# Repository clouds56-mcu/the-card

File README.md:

# The Card — E-Paper Smart Badge

**Website:** <https://clouds56-mcu.github.io/the-card/>

> An **ESP32-S3** based DIY/learning smart badge: e-paper wallpapers, Bluetooth, NFC, multi-button watch-style control, and on-board sensors, worn around the neck like an ID badge.

## 📋 Project Brief

| Item | Spec |
|---|---|
| **Positioning** | DIY / open learning platform (open-source, flashable, well-documented) |
| **MCU** | ESP32-S3-WROOM-1-N16R8 (16 MB Flash + 8 MB Octal PSRAM) |
| **Display** | 2.9" e-paper 296×128 (SSD1680, partial refresh / 4-gray) |
| **Wireless** | Bluetooth 5 LE (on-module) + NFC (ST25DV04KC dynamic tag, etched v0.2 antenna) |
| **Input** | 4× tactile buttons (up/down/select/menu, watch-style) |
| **Sensors** | 6-axis IMU (LSM6DSO) + Temp/Humidity (SHT40) |
| **Power** | 3.7 V Li-Po + USB-C charging + fuel gauge |
| **Wear** | Lanyard badge form factor |

## 📚 Documentation Index

| Doc | Description |
|---|---|
| [docs/architecture.md](docs/architecture.md) | System block diagram, subsystem design, **GPIO pin map** |
| [docs/bom.md](docs/bom.md) | Full BOM (with LCSC part #s / unit prices / links) + cost analysis |
| [docs/power-budget.md](docs/power-budget.md) | State-based power model + battery-life scenarios |
| [website/README.md](website/README.md) | Product site, hardware previews, and candidate release downloads |

## 💰 Key Takeaways

- **Component BOM (incl. panel + battery, excl. PCB/case):** ~$29 (1-off) / ~$21 (@100) / ~$18 (@1k)
- **Landed cost (incl. PCBA + case + assembly):** ~$40 (1-off) / ~$28 (@100) / ~$21 (@1k)
- **Cost driver:** e-paper panel (~$7, 33%) + MCU (~$4, 18%) + battery/IMU (~$2.5 each)
- **Battery life:** ~5.4 months theoretical for modeled daily use (1000 mAh), with ~4–5 months as a planning range; prototype measurement is pending
- **#1 power gotcha:** keep the WS2812 gated; the always-enabled SO-8 ST25DV and ME6211 dominate the revised ~0.16–0.17 mA sleep estimate

## 🚧 Optional Expansion (not in core BOM)

- Microphone (INMP441 / MSM261S) — voice interaction
- Ambient light (BH1750) — auto contrast
- Solar harvesting (paired with ST25DV's EH pin)
- Color e-paper (2.66" R/Y/B/W, slow 11 s refresh)

---

## 📄 License

This project is released under the **[MIT License](LICENSE)** — firmware, hardware designs, and documentation alike. Build it, modify it, ship it.

---

*Prices reflect 2026-08 LCSC / JLCPCB / Good Display market data and are for reference only — confirm at order time.*

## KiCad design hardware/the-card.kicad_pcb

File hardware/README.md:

# hardware/ — Schematic & PCB (KiCad, code-first)

The electrical design of **the-card**, captured in code and emitted as both a
KiCad **schematic** (`.kicad_sch`) and a **netlist** (`.net`). KiCad 10 is
installed; the schematic opens in eeschema and is ERC-clean (0 errors).

```
hardware/
├── parts.yaml              # parts/procurement manifest, kept in sync with circuit.py
├── design_metadata.py      # sole project/design SemVer identity
├── pyproject.toml + uv.lock# uv project: skidl + easyeda2kicad (+ pypdf dev)
├── circuit.py              # the design in SKiDL (connectivity) -> the-card.net
├── gen_hierarchical_schematic.py # current deterministic A2 layout generator
├── gen_pcb.py              # deterministic placement, routing, planes, and keepouts
├── pcb_router.py           # board-specific fanout and deterministic maze routing
├── nfc_antenna.py          # v0.2 coil geometry and first-order RF model
├── verify_schematic.py     # compare every KiCad pin's peers with circuit.py
├── gen_schematic.py        # legacy flat-layout generator; not used currently
├── the-card.kicad_pro      # KiCad 10 project
├── the-card.kicad_sch      # GENERATED single-page A2 schematic
├── the-card.kicad_pcb      # GENERATED four-layer PCB layout
├── the-card.kicad_dru      # project DRC rules, including the NFC quiet area
├── sym-lib-table / fp-lib-table  # register our the-card + passives libraries
├── SCHEMATIC-GUIDE.md      # functional-region drawing and review notes
├── datasheets/             # archived datasheet PDFs + index
├── scripts/fetch_libs.sh   # regenerate libraries/ from LCSC#s in parts.yaml
├── scripts/normalize_libraries.py # reviewed corrections to fetched footprints
├── scripts/release_fabrication.py # checked Gerber/drill/BOM/placement release
├── scripts/export_design_review.py # portable CI schematic/PCB review exports
├── scripts/release_manifest.py # versioned release.json metadata + hashes
├── scripts/rasterize_svg.py # review PNGs from KiCad SVG plots
└── libraries/              # Reviewed 2D libs tracked; generated 3D models ignored
```

## One-time setup

```bash
cd hardware
uv sync                     # create .venv, install skidl + easyeda2kicad
./scripts/fetch_libs.sh     # fetch symbol/footprint/3D for every LCSC part
```

## Generate and verify

```bash
uv run python circuit.py
uv run python gen_hierarchical_schematic.py
uv run python verify_schematic.py
kicad-cli sch erc --severity-all --output /tmp/erc.json --format json the-card.kicad_sch
```

The verifier exports the complete KiCad schematic and compares both the peer
set of every component pin and every explicitly named net with the canonicalized
SKiDL circuit. The expected v0.2.0 result is 78 components and 292 component
pins with identical connectivity across 43 canonical named nets. KiCad ERC has 0
violations.

Generate the PCB layout with KiCad's bundled Python:

```bash
/Applications/KiCad/KiCad.app/Contents/Frameworks/\
Python.framework/Versions/3.9/bin/python3 gen_pcb.py
kicad-cli pcb drc --output /tmp/pcb-drc.json --format json the-card.kicad_pcb
```

The board is a portrait ID-1 outline (53.98 × 85.60 mm), four layers, and
0.8 mm thick. The display and controls are on the front; the ESP32, battery,
sensors, power circuitry, USB-C, and display connector are on the rear. The
generator encodes display, 603048 battery, ESP32 antenna, and NFC keepouts. The
NFC coil occupies a dedicated all-copper-layer RF quiet area: only `NFC_AC0`
and `NFC_AC1` antenna copper is allowed there, with no ground or power plane
beneath it. F.Cu and B.Cu carry local signals over ground pours, In1.Cu is the
primary ground plane, and In2.Cu is the primary 3V3 plane plus longer signal
routes. Ground stitching ties the pours together. The generated board is fully
routed and passes KiCad DRC with 0 violations and 0 unconnected items. Four
non-fabrication reference images are embedded beside the board in PCB Editor,
showing F.Cu, In1.Cu, In2.Cu, and B.Cu simultaneously without affecting plots.

## CI design review

For every CI run, `.github/workflows/ci.yml` publishes a short-lived
`design-review-<commit>` artifact after ERC and DRC pass. It contains the
schematic as PDF/SVG/PNG, a thumbnail, a multipage PCB PDF, and front, inner,
and mirrored back PCB PNGs. These files make schematic and layout changes easy
to inspect without KiCad; they are previews from one commit, not approved
fabrication outputs. The separate `kicad-reports` artifact retains the ERC and
DRC JSON reports, including reports from failed runs when available.

Run the manual `Hardware output` workflow when a complete candidate handoff is
needed. It rebuilds all release gates in the pinned KiCad environment and
uploads the fabrication, preview, assembly, reports, manifest, and checksums as
one 30-day Actions artifact. The workflow does not publish a GitHub Release or
mark the physical approval gates complete.

Build a manufacturing handoff into a new directory after generation:

```bash
uv run python scripts/release_fabrication.py \
  --output ../outputs/the-card-hardware-v0.2.0
```

`DESIGN_VERSION` in `design_metadata.py` is the sole maintained identity. It is
written in full to both KiCad title blocks and release metadata; the constrained
PCB silkscreen derives the matching major/minor mark (`HW 0.2`). Before 1.0, a
physical/electrical/mechanical PCB change advances the minor version, while an
artifact-only correction may advance the patch version. Never overwrite an
already published version. The first physically validated design can become
v1.0.0. The earlier v0.1.0 draft is retained only in Git history because it was
never ordered and contains the NFC issue corrected in v0.2.0.

The release command refuses to overwrite an existing directory or use a dirty
worktree. It runs the connectivity and canonical-net-name verifier, then
requires a clean full DRC, schematic parity check, and ERC. The output tree is:

```text
fabrication/       # Gerbers, PTH/NPTH drills, notes, fabrication-only ZIP
preview/           # schematic/PCB PDFs and PNGs, layer/drill plots, preview ZIP
assembly/
├── canonical/     # normalized BOM/placement CSV+JSON and assembly drawings
└── jlcpcb/        # upload-ready BOM and position CSVs
reports/           # ERC, DRC/parity, and drill reports
release.json       # release identity, provenance, validation, pending approval
SHA256SUMS         # hashes for every artifact and release.json
```

Pass `--include-3d` only when all ignored supplier 3D models referenced by the
board are present and reviewed. Without it, the release remains complete for
fabrication and assembly and uses 2D previews generated from tracked design
files. The internal assembly BOM reports unresolved sourcing explicitly; a
clean board does not imply that every row is ready for a turnkey PCBA order. See
[`FABRICATION.md`](FABRICATION.md) before sending any files to a board house.

`assembly/jlcpcb/bom.csv` follows JLC's eight-column
`Comment, Description, Designator, Footprint, LibRef, Pins, Quantity, JLCPCB Part #`
format. Exact LCSC/JLC codes are written to `JLCPCB Part #` when assigned.
`assembly/jlcpcb/positions.csv` is the matching millimetre CPL with
`Designator, Mid X, Mid Y, Rotation, Layer` and normalized `Top`/`Bottom`
layer names.

Open the schematic:
```bash
/Applications/KiCad/KiCad.app/Contents/MacOS/eeschema the-card.kicad_sch
```

> `gen_hierarchical_schematic.py` is retained under its original filename, but it
> now emits one A2 sheet. It overwrites `the-card.kicad_sch`; put durable layout
> changes into its placement and region-offset tables so regeneration stays
> deterministic. `gen_schematic.py` is the previous flat A1 generator and is
> retained only as a reference.

## How it fits together

`parts.yaml` holds procurement and part data. Its `lcsc_parts` section drives
EasyEDA library fetching, while `assembly_parts` records exact BOM selections
that reuse existing project or KiCad symbols and footprints. An
`assembly_parts` entry with the same reference as an `lcsc_parts` entry
overrides only the procurement selection, allowing a verified pin-compatible
replacement to keep the existing symbol and footprint. `fetch_libs.sh`
builds the two KiCad libraries, while `circuit.py` defines electrical
connectivity and emits `the-card.net`. The layout generator imports that circuit
and changes only its presentation: one A2 page containing Power/USB, MCU,
NFC/sensors, e-paper, and UI
regions. For an electrical change, update `circuit.py`, regenerate the netlist and
schematic, then run `verify_schematic.py` before accepting the result. See
[`FABRICATION.md`](FABRICATION.md) for stackup, ordering, and assembly checks.

Every resistor and capacitor also receives hidden `Related To` and `Function`
properties from `circuit.py`. The single-page schematic shows compact functional
callouts, while KiCad properties and the internal assembly BOM retain the exact
per-reference annotations without crowding the drawing. The layout keeps support
passives beside their related blocks and emits explicit dots at true wire
junctions; visually crossing wires without a dot are not connected.

## Verification status (done)

The originally flagged sections were checked against datasheets (see
`../PROGRESS.md` §7 and the full pinout cross-check). The bare panel's required
SSD1680 booster, 25 V pump capacitors, and 50 V rail bypass network are now
present on the host PCB. Residual
PCB-layout items are:

- **ST25DV04KC antenna** — design v0.2.0 uses a nine-turn, 0.20 mm F.Cu spiral in the
  front-left strip, with a dedicated quiet area on all four copper layers. The
  ST square-equivalent heuristic gives about 4.52 µH; an NXP rectangular-coil
  cross-check brackets about 3.19–3.98 µH and implies roughly 6.1–14.7 pF of
  nominal added capacitance before stray/assembly loading. C29 therefore accepts
  0–22 pF C0G/NP0, but remains unpopulated until measurement. Verify resonance,
  Q, and multi-phone read/write range in the final enclosure; treat more than
  about 15–18 pF, poor Q, or inadequate range as an antenna-respin signal.
- **Display FPC** — J2 is now the verified single-row Hirose
  FH12-24S-0.5SH(55): 24 positions, 0.5 mm pitch, bottom contact, for a 0.30 mm
  FPC. The project footprint numbers its two hold-down tabs 25 and 26 so both
  are tied to ground by the schematic. Rear silkscreen marks pin 1; confirm the
  folded panel orientation with a paper or physical mock-up before ordering.
- **JST-PH battery polarity** — rear silkscreen marks `BAT+` and `BAT-`, but the
  selected pack's cable must still be verified before plugging it in.

The DW01A/HXY 8205A protection stage has been checked against both datasheets:
R9=100 Ω, R10=1 kΩ, DOUT drives G1 on the cell-negative side, and COUT drives
G2 on the pack-negative side.

## Gotchas

- **easyeda2kicad 1.0.1:** `--output` must be **absolute** with
  `--project-relative` (relative paths crash). `fetch_libs.sh` handles this.
- **EasyEDA API 403:** rate-limits after a big batch — re-run in a few minutes.
- **SKiDL reports pin Y inverted** vs KiCad (math y-up vs KiCad y-down); the
  layout generator handles KiCad's screen-coordinate rotations explicitly.
- **ESP32-S3-WROOM-1-N16R8** uses GPIO33–37 for its Octal PSRAM;
  `circuit.py` leaves GPIO35–37 unconnected and uses GPIO16 for `EPD_PWR_EN`.
- The ST25DV SO-8 GPO is open-drain. Design v0.2.0 adds its required 10 kΩ pull-up R17
  and routes `NFC_IRQ` to GPIO21; GPIO3 is deliberately unused because it is a
  strap-sensitive pin.
- The generator sets embedded part pins to `passive` because several EasyEDA
  symbols have incorrect electrical types. `verify_schematic.py` independently
  checks actual connectivity rather than relying on those types.

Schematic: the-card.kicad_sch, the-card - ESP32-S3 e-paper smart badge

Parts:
C1, C4, C7, C10, C11, C12, C14, C15, C16, C17, C18, C19: 100nF; C_0402_1005Metric
C2, C5, C6, C13: 10uF; C_0603_1608Metric
C3, C8, C9: 1uF; C_0603_1608Metric
C20, C21: 4.7uF 25V; C_0805_2012Metric
C22, C23, C24, C25, C26, C27, C28: 1uF 50V; C_0805_2012Metric
C29: DNP 0-22pF C0G/NP0; C_0402_1005Metric; not fitted
D1: WS2812B-MINI; LED-SMD_4P-L3.5-W3.5-TL_WS2812B
D2, D3, D4: LMBR0530T1G; D_SOD-123
J1: TYPE-C-31-M-12; USB-C_SMD-TYPE-C-31-M-12_1
J2: FH12-24S-0.5SH(55); Hirose_FH12-24S-0.5SH_1x24-2MP_P0.50mm_Horizontal
J3: S2B-PH-SM4-TB(LF)(SN); JST_PH_S2B-PH-SM4-TB_1x02-1MP_P2.00mm_Horizontal
L1: XRNR5020-47uH/M 47uH; IND-SMD_L5.0-W5.0_XRNR5020
L2: PCB NFC antenna; NetTie-2_SMD_Pad0.5mm
Q1, Q2: SI2301CDS-T1-GE3; SOT-23-3_L3.0-W1.7-P0.95-LS2.9-BR
Q3: SI1308EDL-T1-GE3; SOT-323_SC-70
R1, R2, R8, R11, R12, R17: 10k; R_0402_1005Metric
R3, R15: 1M; R_0402_1005Metric
R4: 300k; R_0402_1005Metric
R5, R6: 5.1k; R_0402_1005Metric
R7: 2.2k; R_0402_1005Metric
R9: 100; R_0402_1005Metric
R10: 1k; R_0402_1005Metric
R13, R14: 4.7k; R_0402_1005Metric
R16: 2.2; R_1206_3216Metric
SW1, SW2, SW3, SW4: TS-1187A-B-A-B; SW-SMD_4P-L5.1-W5.1-P3.70-LS6.5-TL_H1.5
TP1: +BAT; TestPoint_Pad_D1.0mm
TP2: BAT_NEG; TestPoint_Pad_D1.0mm
TP3: +3V3; TestPoint_Pad_D1.0mm
TP4: GND; TestPoint_Pad_D1.0mm
TP5: EN; TestPoint_Pad_D1.0mm
TP6: IO0; TestPoint_Pad_D1.0mm
U1: ESP32-S3-WROOM-1-N16R8; WIRELM-SMD_ESP32-S3-WROOM-1
U2: ST25DV04KC-IE8S3; SO-8_L4.9-W3.9-P1.27-LS6.0-BL
U3: LSM6DSOTR; LGA-14_L3.0-W2.5-P0.50-TL
U4: SHT40-BD1B-R2; DFN-4_L1.5-W1.5-P0.80-TL-EP
U5: MAX17048G+T10; TDFN-8_L2.0-W2.0-P0.50-BL-EP1.2
U6: TP4056_C382139; ESOP-8_L4.9-W3.9-P1.27-LS6.0-BL-EP
U7: DW01A_C18164398; SOT-23-6_L2.9-W1.6-P0.95-LS2.8-BR
U8: 8205A; TSSOP-8_L4.4-W3.0-P0.65-LS6.4-BL-2; MPN 8205A; LCSC Part C5148694
U9: ME6211C33M5G-N; SOT-23-5_L3.0-W1.7-P0.95-LS2.8-BL
U10: USBLC6-2SC6; SOT-23-6_L2.9-W1.6-P0.95-LS2.8-BL

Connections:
+3V3: C1.1, C2.1, C9.1, C11.1, C12.1, C13.1, C14.1, Q1.2 (S), Q2.2 (S), R1.1, R2.1, R8.1, R11.1, R12.1, R13.1, R14.1, R17.1, TP3.1, U1.2 (3V3), U2.8 (VCC), U3.5 (VDDIO), U3.8 (VDD), U3.12 (CS), U4.3 (VDD), U9.5 (VOUT)
+BAT: C6.1, C8.1, C10.1, J3.1, R3.1, R9.1, TP1.1, U5.2 (CELL), U5.3 (VDD), U6.5 (BAT), U9.1 (VIN), U9.3 (CE)
AUX_3V3: C15.1, D1.1 (VDD), Q1.3 (D)
BAT_NEG: C7.2, J3.2, TP2.1, U7.6 (VSS), U8.2 (S1), U8.3 (S1)
BTN_DOWN: C17.1, SW2.1 (A), U1.5 (IO5)
BTN_MENU: C19.1, SW4.1 (A), U1.7 (IO7)
BTN_SEL: C18.1, SW3.1 (A), U1.6 (IO6)
BTN_UP: C16.1, SW1.1 (A), U1.4 (IO4)
EPD_BUSY: J2.9, U1.19 (IO11)
EPD_CS: J2.12, U1.20 (IO12)
EPD_DC: J2.11, U1.21 (IO13)
EPD_GDR: J2.2, Q3.1 (G), R15.1
EPD_PUMP: C21.1, D2.1 (K), D3.2 (A)
EPD_PWR_EN: Q2.1 (G), R12.2, U1.9 (IO16)
EPD_RESE: J2.3, Q3.2 (S), R16.1
EPD_RST: J2.10, U1.22 (IO14)
EPD_SCLK: J2.13, U1.18 (IO10)
EPD_SDA: J2.14, U1.17 (IO9)
EPD_SW: C21.2, D4.2 (A), L1.2, Q3.3 (D)
EPD_VCI: C20.1, J2.15, J2.16, L1.1, Q2.3 (D)
EPD_VCOM: C28.1, J2.24
EPD_VDD_CORE: C22.1, J2.18
EPD_VGH: C25.1, D4.1 (K), J2.21
EPD_VGL: C27.1, D2.2 (A), J2.23
EPD_VSH1: C24.1, J2.20
EPD_VSH2: C23.1, J2.5
EPD_VSL: C26.1, J2.22
FET_DRAIN: U8.1 (D12), U8.8 (D12)
GND: C1.2, C2.2, C3.2, C4.2, C5.2, C6.2, C8.2, C9.2, C10.2, C11.2, C12.2, C13.2, C14.2, C15.2, C16.2, C17.2, C18.2, C19.2, C20.2, C22.2, C23.2, C24.2, C25.2, C26.2, C27.2, C28.2, D1.3 (VSS), D3.1 (K), J1.1 (EH), J1.2 (EH), J1.3 (EH), J1.4 (EH), J1.A1B12 (GND), J1.B1A12 (GND), J2.8, J2.17, J2.25, J2.26, R4.2, R5.2, R6.2, R7.2, R10.1, R15.2, R16.2, SW1.3 (C), SW2.3 (C), SW3.3 (C), SW4.3 (C), TP4.1, U1.1 (GND), U1.40 (GND), U1.41 (GND), U2.4 (VSS), U3.1 (SDO/SA0), U3.6 (GND), U3.7 (GND), U4.4 (VSS), U5.1 (CTG), U5.4 (GND), U5.6 (QSTRT), U5.9 (EP), U6.1 (TEMP), U6.3 (GND), U6.9 (EP), U8.6 (S2), U8.7 (S2), U9.2 (VSS), U10.2
I2C_SCL: R13.2, U1.12 (IO8), U2.6 (SCL), U3.13 (SCL), U4.2 (SCL), U5.7 (SCL)
I2C_SDA: R14.2, U1.11 (IO18), U2.5 (SDA), U3.14 (SDA), U4.1 (SDA), U5.8 (SDA)
IMU_INT: U1.38 (IO2), U3.4 (INT1)
LED_DIN: D1.4 (DIN), U1.25 (IO48)
MCU_BOOT: R2.2, TP6.1, U1.27 (IO0)
MCU_EN: C3.1, R1.2, TP5.1, U1.3 (EN)
NFC_AC0: C29.1, L2.1, U2.2 (AC0)
NFC_AC1: C29.2, L2.2, U2.3 (AC1)
NFC_IRQ: R17.2, U1.23 (IO21), U2.7 (GPO)
unnamed: J1.A5 (CC1), R5.1
unnamed: J1.B5 (CC2), R6.1
unnamed: J1.A7 (DN1), J1.B7 (DN2), U10.1
unnamed: J1.A6 (DP1), J1.B6 (DP2), U10.3
unnamed: C4.1, R3.2, R4.1, U1.39 (IO1)
unnamed: R7.1, U6.2 (PROG)
unnamed: U7.3 (COUT), U8.5 (G2)
unnamed: U7.1 (DOUT), U8.4 (G1)
unnamed: C7.1, R9.2, U7.5 (VDD)
unnamed: R10.2, U7.2 (VM)
PWR_AUX: Q1.1 (G), R11.2, U1.24 (IO47)
USB_DM: U1.13 (IO19), U10.6
USB_DP: U1.14 (IO20), U10.4
VBUS: C5.1, J1.A4B9 (VBUS), J1.B4A9 (VBUS), U6.4 (VCC), U6.8 (CE), U10.5
~CHRG: R8.2, U1.8 (IO15), U6.7 (~CHRG)

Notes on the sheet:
USB-C input, ESD, and charger
3.3 V regulation and fuel gauge
Cell protection
Switched peripheral rails
J1/U10 support: R5/R6 CC pull-downs; C5 USB input bulk
U6 support: R7 charge-current set; R8 CHRG pull-up; C5/C6 bulk
U9/U5 support: C8/C9 LDO stability; C10 fuel-gauge bypass
U7/U8 support: R9 supply feed; R10 pack sense; C7 bypass
Q1/Q2 support: R11/R12 gate pull-ups (rails default off)
Controller, boot straps, decoupling, and battery ADC
Named labels keep long inter-block connections readable.
C1/C2 -> U1: 3V3 bypass + bulk; R1/C3 -> U1 EN: pull-up + startup timing
R2 -> U1 IO0: boot pull-up; R3/R4/C4 -> U1 IO1: battery divider + filter
NFC dynamic tag
Motion and environmental sensors
I2C pull-ups
C11 -> U2: NFC bypass; R17 -> GPO pull-up; C29 -> RF trim (DNP)
R13/R14 -> I2C bus U1-U5: SCL/SDA pull-ups
C12/C13 -> U3: IMU bypass + bulk
C14 -> U4: environmental-sensor bypass
GDEY029T94 24-pin FPC interface
Booster and boosted gate rails
J2 panel connector and direct rail reservoirs
C20/L1: VCI input; C21/D2-D4/Q3: boost conversion
R15/R16: Q3 gate pull-down and current sense
C22-C24/C26/C28: direct J2 rail reservoirs
C25/C27: boosted VGH/VGL reservoirs
User buttons with hardware debounce
Status LED
C16-C19 -> SW1-SW4/U1: button debounce
C15 -> D1: LED supply bypass

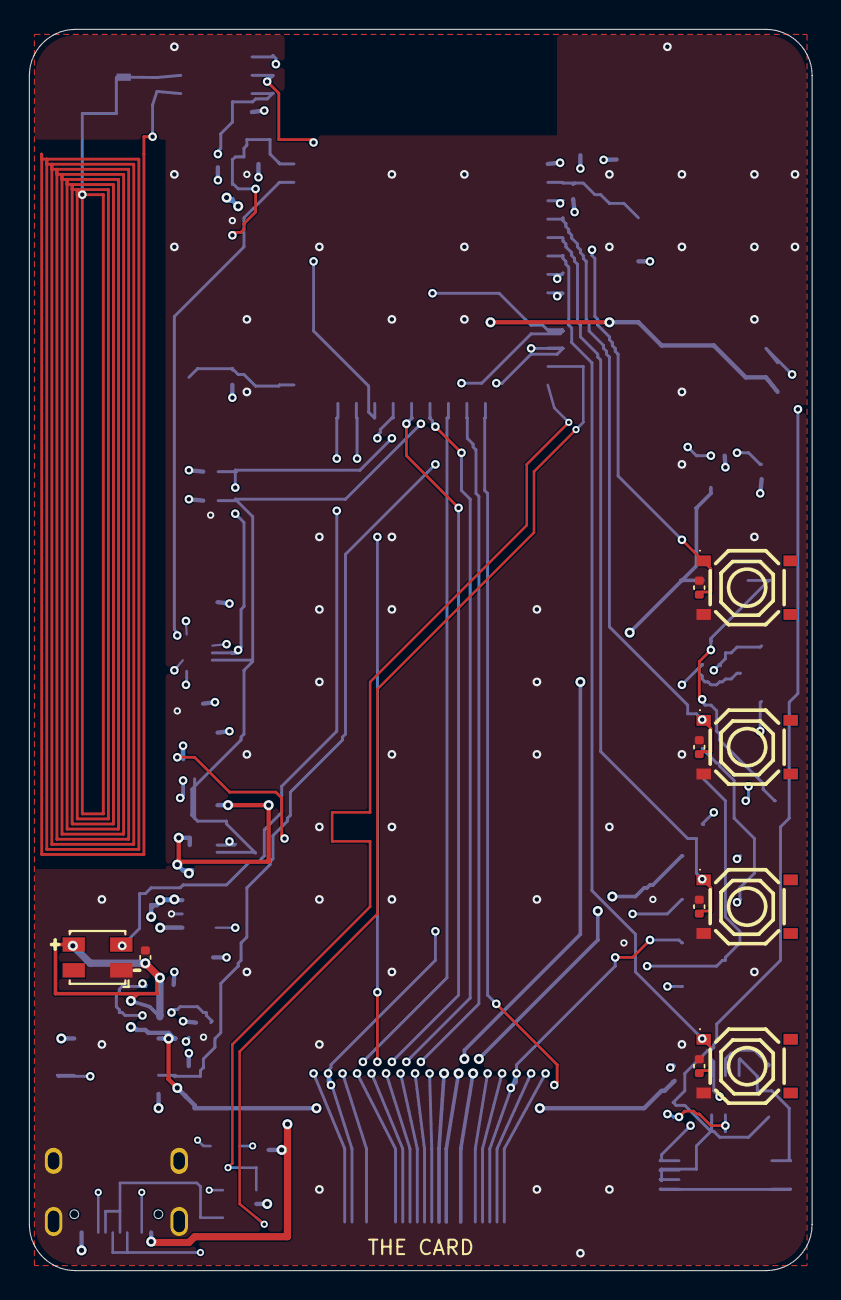
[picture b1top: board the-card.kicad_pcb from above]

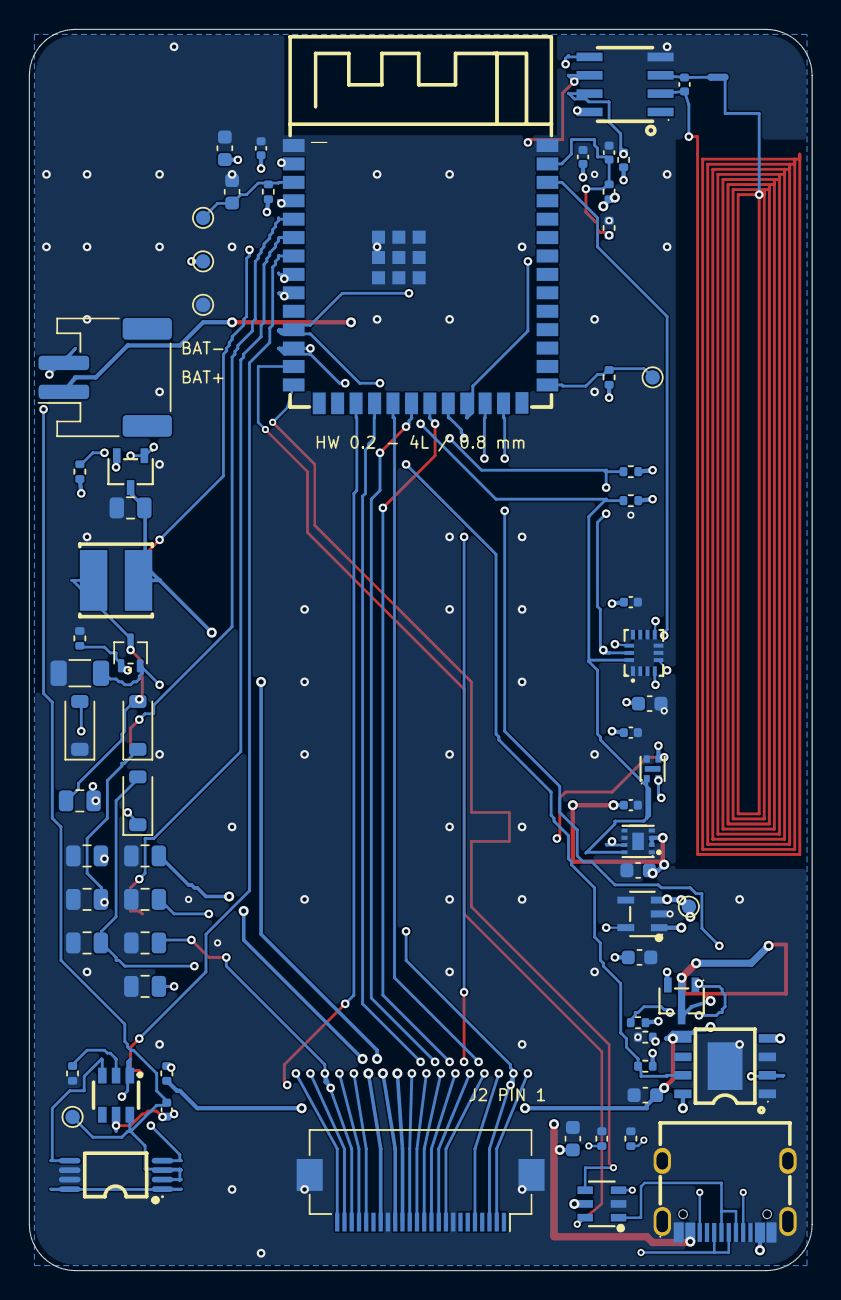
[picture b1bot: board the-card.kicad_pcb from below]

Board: 4 copper layers, 54.0 x 85.6 mm, 78 parts (68 on the bottom side), 53 nets.

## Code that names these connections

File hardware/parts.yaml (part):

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    name: S2B-PH-SM4-TB(LF)(SN)
    lcsc: C295747
    source_hint: JLCPCB Extended
    role: 1S battery connector (pin 1 +BAT, pin 2 BAT_NEG)
    footprint: "Connector_JST:JST_PH_S2B-PH-SM4-TB_1x02-1MP_P2.00mm_Horizontal"
    note: Right-angle SMT JST-PH. Battery cable polarity is not standardized; inspect the actual pack.
  - ref: L1
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    6:  NC            # keep open
    7:  NC            # keep open
    8:  GND           # BS1 = L  -> 4-wire SPI
    9:  EPD_BUSY      # BUSY     (GPIO11)
    10: EPD_RST       # RES#     (GPIO14)
    11: EPD_DC        # D/C#     (GPIO13)
    12: EPD_CS        # CS#      (GPIO12)
    13: EPD_SCLK      # SCL      (GPIO10)
    14: EPD_SDA       # SDA/MOSI (GPIO9)
    15: EPD_VDDIO     # tie to VCI
    16: EPD_VCI       # +3V3 (switched via Q2)
    17: GND           # VSS
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  "+BAT": "Battery cell positive, 3.0–4.2V"
  BAT_NEG: "Battery cell negative before the protection FETs; not system ground"
  "+3V3": "System rail from ME6211 LDO (always on)"
  AUX_3V3: "Switchable branch rail via Q1 (P-MOSFET, PWR_AUX=GPIO47) — status LED only"
  EPD_VCI: "Switchable e-paper VCI/VDDIO and booster input via Q2"

# ─────────────────────────────────────────────────────────────────────────────
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
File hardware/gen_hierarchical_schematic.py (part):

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      "U8": p(105, 128, 90),
      "R_dvcc": p(48, 118),
      "R_dvm": p(92, 130, 180),
      # Both pins face outward: VDD above and BAT_NEG directly on the trunk.
      "C_dprot": p(58, 138, 270),
      "Q1": p(185, 130),
      "R_q1g": p(176, 116, 270),
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# component pin. Endpoint keys are explicit so a circuit change cannot silently
# alter the drawing convention.
NET_LABEL_CLUSTERS = {
  # EPD_VCI crosses the power and e-paper regions. Keep the two J2 pins as
  # compact label stubs, but wire C20 directly to the L1 input locally.
  ("epaper", "EPD_VCI"): (
    (("J2", "15"),),
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
# The 8205A exposes its common drain on two opposite pins. Repeated labels
# communicate that internal node without drawing a misleading wire through the body.
LABEL_EACH_LOCAL_NETS = {("power_usb", "FET_DRAIN")}

# Explicit trunks keep the interleaved reversible USB-C data pins readable.
TRUNK_ROUTES = {
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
